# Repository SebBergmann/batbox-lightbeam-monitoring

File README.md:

# Arduino-basierte Lichtschranke zum Monitoring von Fledermaus-Kastenquartieren

Dieses Repository enthält die wesentlichen Dateien zum Nachbau eines kostengünstigen, Arduino-Nano-basierten Lichtschrankensystems zur automatisierten Erfassung von Aktivität an Fledermaus-Kastenquartieren.

Das System überwacht einen Infrarot-Lichtstrahl zwischen Sende- und Empfängerdiode. Wird der Lichtstrahl unterbrochen, werden fortlaufend Zeitstempel auf einer SD-Karte gespeichert. Sobald der Lichtstrahl wieder frei ist, endet die Aufzeichnung. Das System ist als Ergänzung zu Sichtkontrollen gedacht; Individuenzahl, Flugrichtung und Art können damit nicht bestimmt werden.

## Inhalt des Repositorys

- `hardware/kicad/` – KiCad-Dateien der Platine
- `hardware/gerber/` – Gerber- und Bohrdateien für die PCB-Fertigung
- `software/` – Arduino-Sketch
- `BOM/` – Stückliste
- `images/` – Fotos und Abbildungen des Aufbaus
- Quick Start Guide – Aufbau, Bedienung und Softwareinstallation

## 1. Platine

Die Platine wurde in KiCad erstellt. Die Datei

`lightbeam.kicad_pcb`

enthält das vollständige Platinenlayout und kann bei Herstellern, die native KiCad-Dateien unterstützen, direkt zur Fertigung verwendet werden.

Zusätzlich stehen Gerber- und Bohrdateien zur Verfügung. Für eine herstellerunabhängige Bestellung kann die Datei

`lightbeam_gerber.zip`

verwendet werden. Sie enthält die Kupferlagen, Lötstoppmasken, Bestückungsdrucke, Platinenkontur sowie PTH- und NPTH-Bohrdateien.

## 2. Hauptkomponenten

Das System besteht im Wesentlichen aus:

- Arduino Nano mit ATmega328P
- Infrarot-Sendediode
- Empfängerdiode
- Status-LED
- Hauptschalter und LED-Schalter
- Step-Down-Spannungswandler
- Real-Time Clock (RTC)
- SD-Karten-Modul
- externer Stromversorgung

Die vollständige Stückliste mit Spezifikationen befindet sich im Ordner `BOM/`.

Beim Anschluss von Sende- und Empfängerdiode unbedingt auf die korrekte Polarität achten. Eine falsche Polung kann die Bauteile beschädigen. Sender und Empfänger müssen mit einem maximalen Abstand von 35 cm direkt aufeinander ausgerichtet werden.

## 3. Arduino-Firmware

Der Sketch befindet sich unter:

`software/Lightbeam.ino`

Benötigte Bibliotheken:

- `Wire.h`
- `SPI.h`
- `SD.h`
- `Sodaq_DS3231.h`

## 4. Echtzeituhr einstellen

Vor dem ersten Einsatz muss die RTC auf Datum und Uhrzeit des Computers gesetzt werden.

Für den ersten Upload diese beiden Zeilen im Sketch aktivieren:

`DateTime dt(__DATE__, __TIME__);`
`rtc.setDateTime(dt);`

Sketch hochladen. Anschließend beide Zeilen wieder auskommentieren:

`//DateTime dt(__DATE__, __TIME__);`
`//rtc.setDateTime(dt);`

Danach den Sketch ein zweites Mal hochladen. So wird verhindert, dass die RTC bei jedem Neustart erneut auf den Zeitpunkt der Kompilierung gesetzt wird.

## 5. Inbetriebnahme

1. SD-Karte einsetzen.
2. Sende- und Empfängerdiode korrekt anschließen und aufeinander ausrichten.
3. Stromversorgung anschließen.
4. Falls nötig, Hauptschalter einschalten.
5. LED-Schalter einschalten und Status prüfen.

Beim Start:

- grün blinkend: SD-Karte wird initialisiert
- rot blinkend: SD-Karte wurde nicht erkannt

Im Messbetrieb:

- LED aus: Lichtstrahl ist frei und Sender/Empfänger sind korrekt ausgerichtet
- grün dauerhaft: Lichtstrahl ist unterbrochen oder Sender/Empfänger sind nicht korrekt ausgerichtet

Nach erfolgreicher Kontrolle kann der LED-Schalter ausgeschaltet werden, um Energie zu sparen. Die Datenerfassung läuft weiter.

Vor dem Entfernen der SD-Karte das System über Hauptschalter A ausschalten. Wird die SD-Karte während des Betriebs entfernt, muss das System anschließend neu gestartet werden.

## 6. Datenspeicherung

Die Daten werden in der Datei

`BATBOX.LOG`

auf der SD-Karte gespeichert und bei jeder neuen Sitzung ergänzt.

Beim Start wird unter anderem ein Eintrag mit `started` geschrieben. Bei einer Unterbrechung wird Datum, Uhrzeit und `interruption` gespeichert, zum Beispiel:

`Date,Time,Light_Beam,Others`
`09.10.2026,18:30:01,,started`
`09.10.2026,19:04:23,interruption,`

Solange der Lichtstrahl unterbrochen bleibt, schreibt der aktuelle Sketch fortlaufend weitere Zeitstempel. Eine längere Unterbrechung erzeugt daher mehrere Einträge. Bei Auswertungen können diese beispielsweise zu Aktivitätsminuten zusammengefasst werden.

Die Logdatei kann als Textdatei geöffnet oder unter anderem in Excel oder R importiert werden.

## 7. Stromversorgung

Das System verwendet einen Step-Down-Spannungswandler, der je nach Spezifikation Eingangsspannungen z.B. von 7–24 V auf die benötigten 5 V reduziert. Im beschriebenen Aufbau wird ein Batteriehalter für acht Mono-D-Batterien verwendet; andere geeignete Spannungsquellen im Bereich von 7–24 V sind ebenfalls möglich.

Handelsübliche Powerbanks sind nur eingeschränkt geeignet, da viele Modelle bei geringer Stromaufnahme automatisch abschalten.

## 8. Grenzen des Systems

Die Lichtschranke erfasst ausschließlich Unterbrechungen des Lichtstrahls. Ohne zusätzliche Beobachtungen lassen sich daraus weder die Anzahl der Tiere noch Ein- und Ausflugrichtung oder Artzugehörigkeit bestimmen. Auch andere Tiere oder Objekte können Ereignisse auslösen.

Das System ist daher als kostengünstige Ergänzung zu weiteren Monitoringmethoden zu verstehen.

## 9. Version, Zitierung und Lizenz

Falls das System für wissenschaftliche Arbeiten verwendet wird, bitte die zugehörige Publikation zitieren:
Bergmann & Knörnschild (2026): Bau Arduino-basierter Lichtschranken zum Monitoring von Kastenquartieren. Nyctalus. 

## Kontakt

Anja Bergmann 
Anja [at] bergmann-email.de

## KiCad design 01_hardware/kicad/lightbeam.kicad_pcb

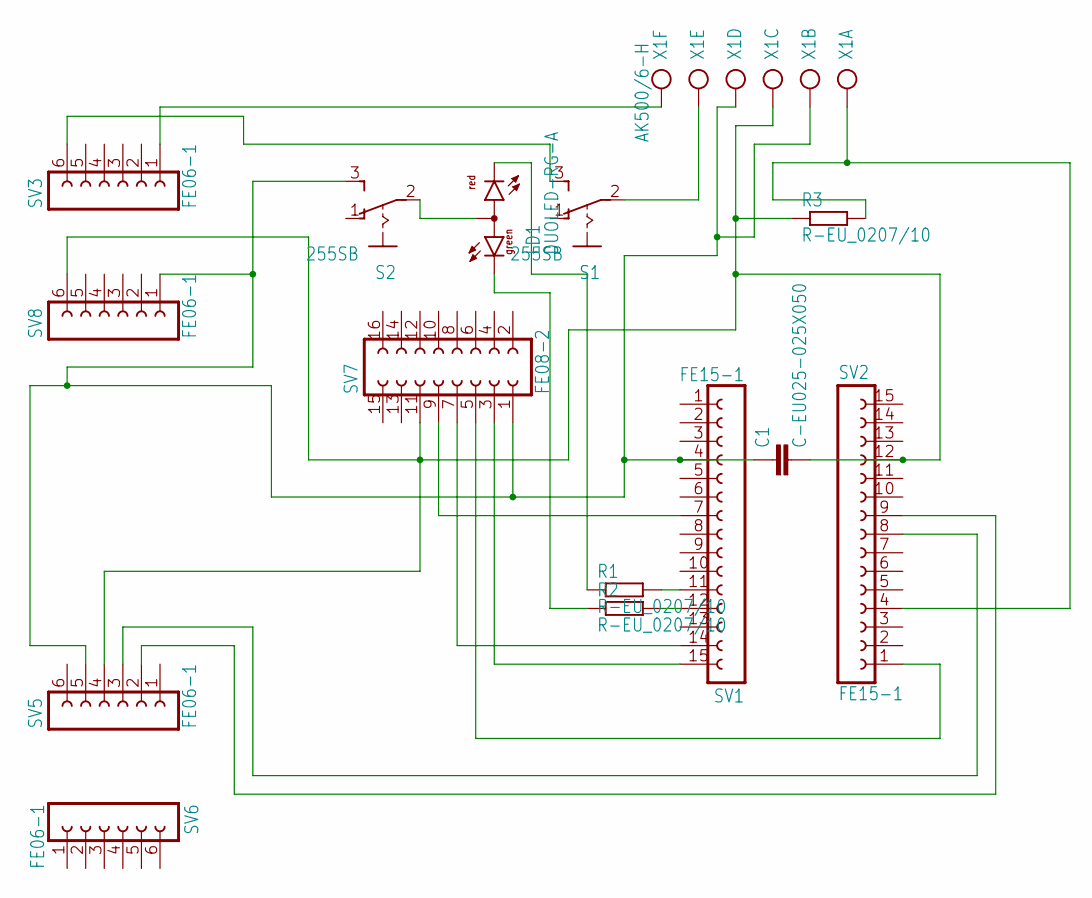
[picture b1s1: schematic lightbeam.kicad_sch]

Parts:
C1: C-EU025-025X050; C025-025X050
LD1: DUOLED-RG-A; DUOLED-A-5MM
R1, R2, R3: R-EU_0207/10; 0207_10
S1, S2: 255SB
SV1, SV2: FE15-1; FE15
SV3, SV5, SV6, SV8: FE06-1; FE06
SV7: FE08-2
X1: AK500/6-H; AK500_6-H

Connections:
unnamed: LD1.CX (CG), R2.1
unnamed: LD1.CR, R1.1
unnamed: R1.2, SV1.11
unnamed: R2.2, SV1.12
unnamed: S1.2, X1.5 (KL)
unnamed: S1.3 (S), SV3.6
unnamed: LD1.A, S2.2
unnamed: C1.1, S2.3 (S), SV1.4, SV5.5, SV7.1, SV8.1, X1.2 (KL), X1.4 (KL)
unnamed: SV1.7, SV7.9
unnamed: SV1.14, SV7.7
unnamed: SV1.15, SV7.3
unnamed: SV2.1, SV7.5
unnamed: SV2.8, SV5.3
unnamed: SV2.9, SV5.2
unnamed: R3.2, SV2.4, X1.1 (KL)
unnamed: C1.2, R3.1, SV2.12, SV5.4, SV7.11, SV8.6, X1.3 (KL)
unnamed: SV3.1, X1.6 (KL)

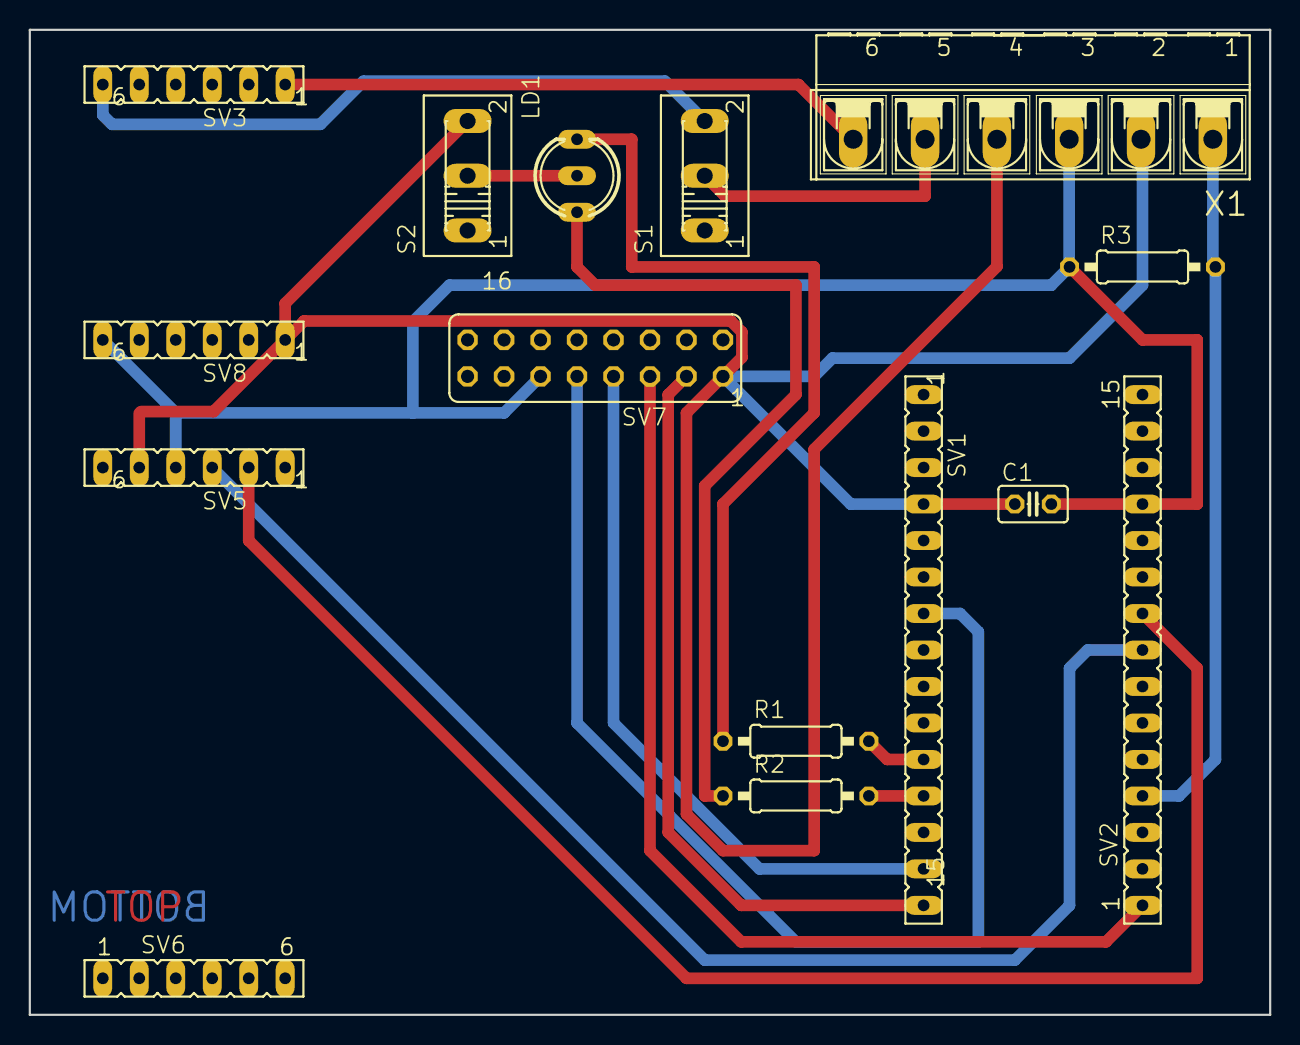
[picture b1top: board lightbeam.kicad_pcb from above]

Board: 2 copper layers, 86.4 x 68.6 mm, 15 parts (0 on the bottom side), 17 nets.
